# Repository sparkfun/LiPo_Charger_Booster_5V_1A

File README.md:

SparkFun LiPo Charger/Booster - 5V/1A
========================================

[*SparkFun LiPo Charger/Booster - 5V/1A (PRT-14411)*](https://www.sparkfun.com/products/14411)

The SparkFun 5V/1A LiPo Charger/Booster is a no-nonsense circuit for generating one amp from a Lithium Polymer battery at 5V.

Repository Contents
-------------------

* **/Documentation** - Data sheets, additional product information
* **/Hardware** - Eagle design files (.brd, .sch)
* **/Production** - Production panel files (.brd)

Documentation
--------------
* **[SparkFun Fritzing Part](https://github.com/sparkfun/Fritzing_Parts/blob/main/products/14411_sfe_LiPo_Charger_Booster-5V1A.fzpz)** - Fritzing diagrams for SparkFun products.
* **[Hookup Guide](https://learn.sparkfun.com/tutorials/sparkfun-5v1a-lipo-chargerbooster-hookup-guide)** - Basic hookup guide for the SparkFun LiPo Charger/Booster - 5V/1A.

Product Versions
----------------
* [PRT-14411](https://www.sparkfun.com/products/14411)- LiPo Charger/Booster 5V/1A

Version History
----------------
* [HW-V1.0](https://github.com/sparkfun/LiPo_Charger_Booster_5V_1A/releases/tag/HW-V1.0) 

License Information
-------------------

This product is _**open source**_! 

Please review the LICENSE.md file for license information. 

If you have any questions or concerns on licensing, please contact techsupport@sparkfun.com.

Distributed as-is; no warranty is given.

- Your friends at SparkFun.

_<COLLABORATION CREDIT>_

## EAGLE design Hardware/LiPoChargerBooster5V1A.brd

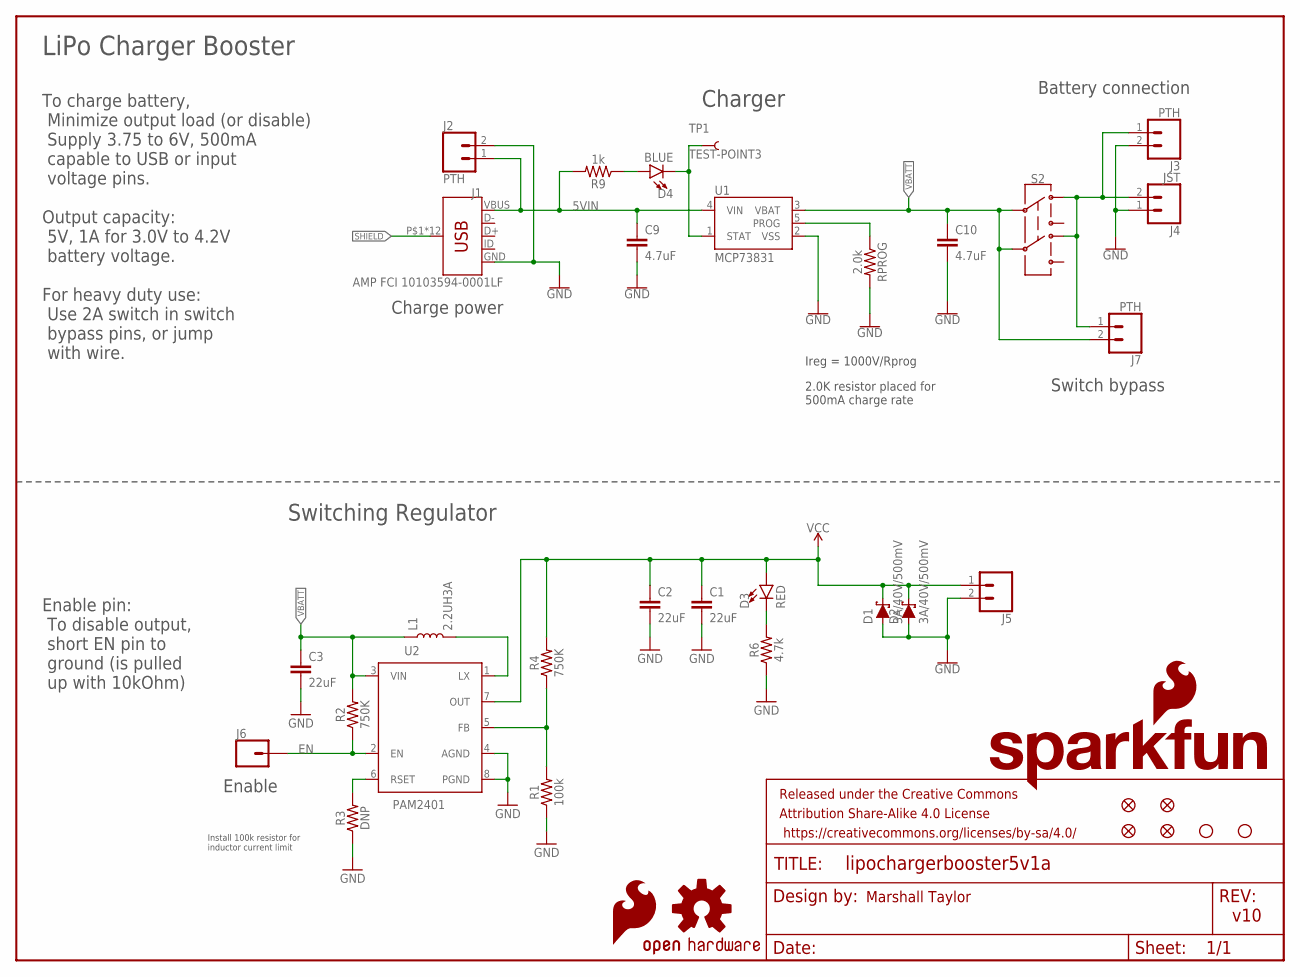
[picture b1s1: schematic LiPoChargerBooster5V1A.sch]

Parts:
C1, C2, C3: 22uF; 0805
C9, C10: 4.7uF; 0603
D1, D2: 3A/40V/500mV; SMA-DIODE
D3: RED; LED-0603
D4: BLUE; LED-0603
FRAME1: FRAME-LETTER; CREATIVE_COMMONS
J1: AMP FCI 10103594-0001LF; USB-MICROB-PTH
J2, J3, J7: PTH; 1X02
J4: JST; JST-2-SMD
J5: CONN_02; 1X02
J6: CONN_01; 1X01
JP1, JP2, JP4, JP16: FIDUCIAL1X2; FIDUCIAL-1X2
JP3: SFE_LOGO_NAME_FLAME.1_INCH; SFE_LOGO_NAME_FLAME_.1
JP6, JP7: STAND-OFF
L1: 2.2UH3A; INDUCTOR_4X4MM
LOGO1: SFE_LOGO_FLAME.1_INCH; SFE_LOGO_FLAME_.1
R1: 100k; 0603
R2, R4: 750K; 0603
R3: DNP; 0603
R6: 4.7k; 0603
R9: 1k; 0603
RPROG: 2.0k; 0603
S2: SWITCH-DPDT-SMD-AYZ0202; SWITCH_DPDT_SMD_AYZ0202
TP1: TEST-POINT3; PAD.03X.03
U1: MCP73831; SOT23-5
U2: PAM2401; MSOP8
U$1: OSHW-LOGOS; OSHW-LOGO-S

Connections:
5VIN: C9.1, J1.VBUS, J2.1, R9.2, U1.4 (VIN)
EN: J6.1, R2.1, U2.2 (EN)
GND: C1.2, C2.2, C3.2, C9.2, C10.2, D1.A, D2.A, J1.GND, J2.2, J3.2, J4.1 (2), J5.2, R1.1, R3.1, R6.1, RPROG.2, U1.2 (VSS), U2.4 (AGND), U2.8 (PGND)
unnamed: D3.C, R6.2
unnamed: D4.A, R9.1
unnamed: L1.P$2 (2), U2.1 (LX)
unnamed: R3.2, U2.6 (RSET)
unnamed: J3.1, J4.2 (1), J7.1, S2.1, S2.4
unnamed: RPROG.1, U1.5 (PROG)
unnamed: R1.2, R4.1, U2.5 (FB)
unnamed: D4.C, TP1.P$1, U1.1 (STAT)
SHIELD: J1.P$1 (SHIELD), J1.P$2 (SHIELD), J1.P$3 (SHIELD), J1.P$4 (SHIELD), J1.P$6 (SHIELD), J1.P$8 (SHIELD), J1.P$10 (SHIELD), J1.P$12 (SHIELD), J1.SHEILD2 (SHIELD), J1.SHIELD, J1.SHIELD3 (SHIELD), J1.SHIELD4 (SHIELD)
VBATT: C3.1, C10.1, J7.2, L1.P$1 (1), R2.2, S2.2, S2.5, U1.3 (VBAT), U2.3 (VIN)
VCC: C1.1, C2.1, D1.C, D2.C, D3.A, J5.1, R4.2, U2.7 (OUT)

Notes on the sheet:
Charger
Switching Regulator
Marshall Taylor
v10
2.0K resistor placed for 500mA charge rate
Ireg = 1000V/Rprog
To charge battery, Minimize output load (or disable) Supply 3.75 to 6V, 500mA capable to USB or input voltage pins.
Install 100k resistor for inductor current limit
LiPo Charger Booster
Output capacity: 5V, 1A for 3.0V to 4.2V battery voltage.
Enable pin: To disable output, short EN pin to ground (is pulled up with 10kOhm)
Enable
Charge power
Battery connection
Switch bypass
For heavy duty use: Use 2A switch in switch bypass pins, or jump with wire.

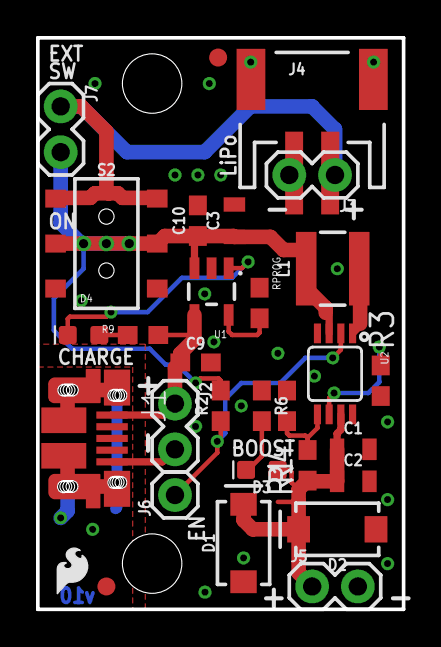
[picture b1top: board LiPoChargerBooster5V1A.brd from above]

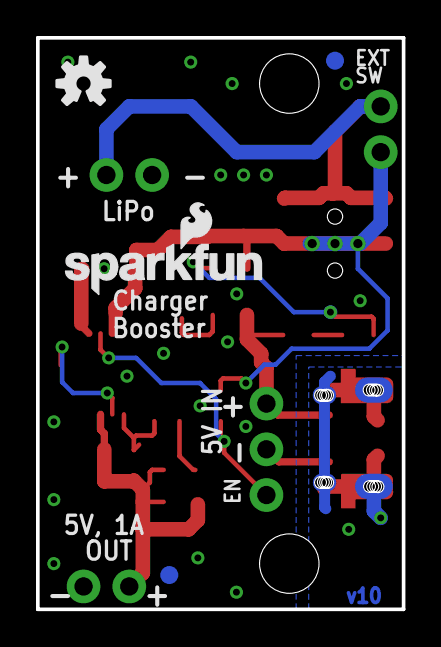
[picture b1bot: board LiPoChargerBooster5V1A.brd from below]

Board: 2 copper layers, 20.3 x 31.8 mm, 38 parts (5 on the bottom side), 14 nets.

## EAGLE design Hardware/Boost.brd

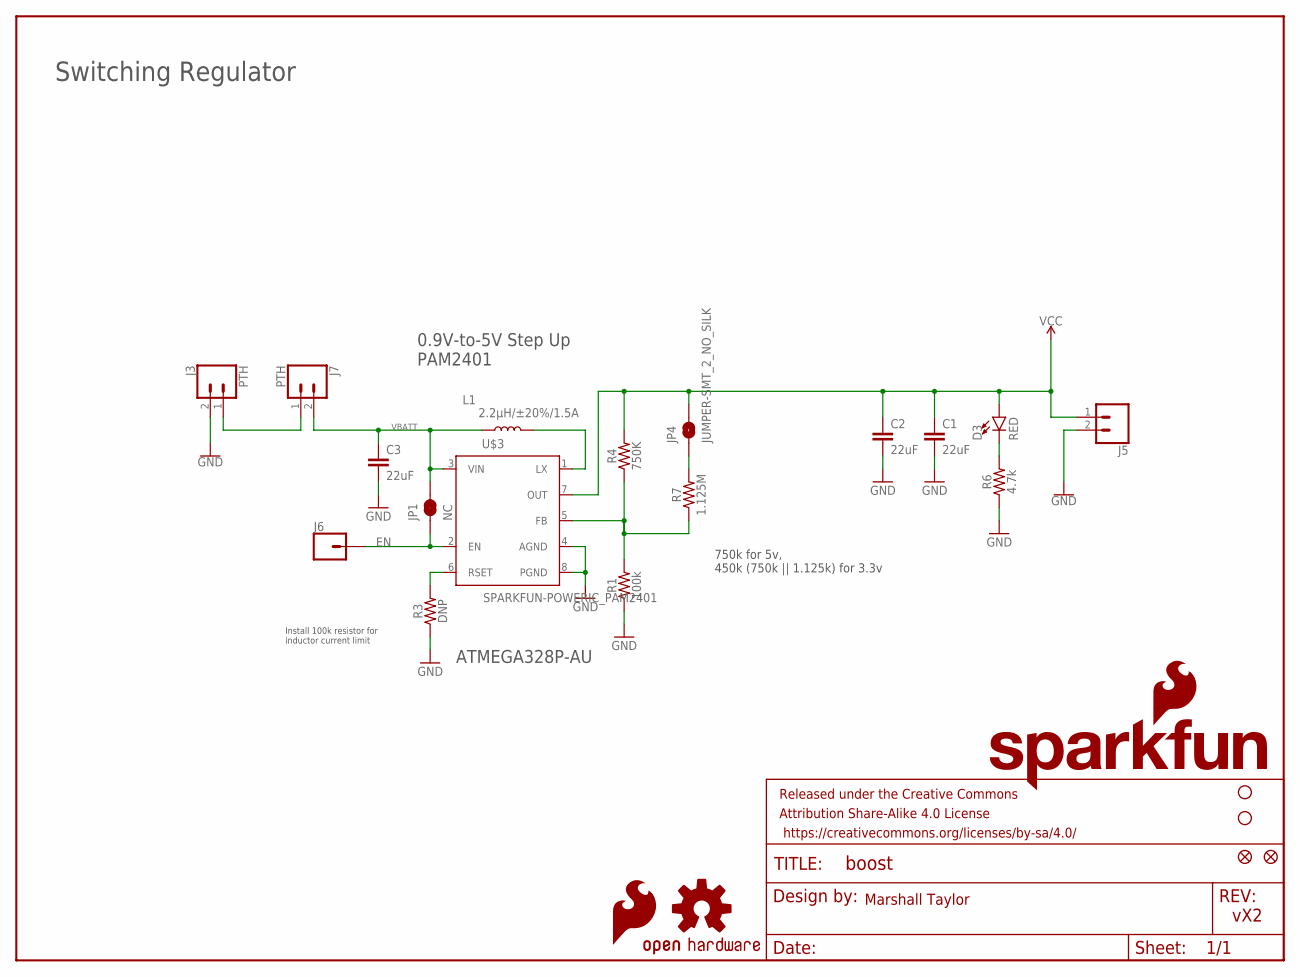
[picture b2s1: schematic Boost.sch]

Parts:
C1, C2, C3: 22uF; 0805
D3: RED; LED-0603
FRAME1: FRAME-LETTER; CREATIVE_COMMONS
J3, J7: PTH; 1X02_NO_SILK
J5: CONN_021X02_NO_SILK; 1X02_NO_SILK
J6: CONN_01; 1X01
JP1: NC; SMT-JUMPER_2_NC_TRACE_NO-SILK
JP2, JP16: FIDUCIAL1X2; FIDUCIAL-1X2
JP3: SFE_LOGO_NAME_FLAME.1_INCH; SFE_LOGO_NAME_FLAME_.1
JP4: JUMPER-SMT_2_NO_SILK; SMT-JUMPER_2_NO_SILK
JP6, JP7: STAND-OFF
L1: 2.2µH/±20%/1.5A; INDUCTOR_2.2UHCOPY
LOGO1: SFE_LOGO_FLAME.1_INCH; SFE_LOGO_FLAME_.1
R1: 100k; 0603
R3: DNP; 0603
R4: 750K; 0603
R6: 4.7k; 0603
R7: 1.125M; 0603
U$1: OSHW-LOGOS; OSHW-LOGO-S
U$3: SPARKFUN-POWERIC_PAM2401; SPARKFUN-POWERIC_MSOP8

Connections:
EN: J6.1, JP1.1, U$3.2 (EN)
GND: C1.2, C2.2, C3.2, J3.2, J5.2, R1.1, R3.1, R6.1, U$3.4 (AGND), U$3.8 (PGND)
unnamed: JP4.1, R7.2
unnamed: D3.C, R6.2
unnamed: L1.P$2 (2), U$3.1 (LX)
unnamed: R3.2, U$3.6 (RSET)
unnamed: J3.1, J7.1
unnamed: R1.2, R4.1, R7.1, U$3.5 (FB)
VBATT: C3.1, J7.2, JP1.2, L1.P$1 (1), U$3.3 (VIN)
VCC: C1.1, C2.1, D3.A, J5.1, JP4.2, R4.2, U$3.7 (OUT)

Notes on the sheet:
Switching Regulator
Marshall Taylor
vX2
0.9V-to-5V Step Up PAM2401
ATMEGA328P-AU
Install 100k resistor for inductor current limit
750k for 5v, 450k (750k || 1.125k) for 3.3v

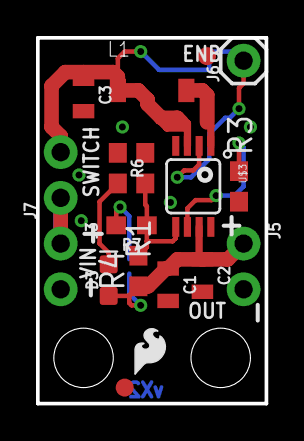
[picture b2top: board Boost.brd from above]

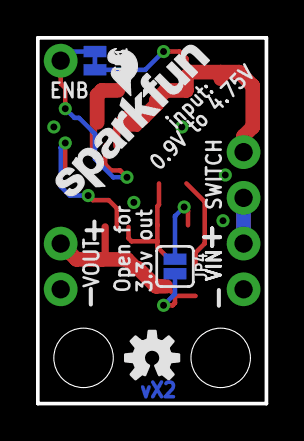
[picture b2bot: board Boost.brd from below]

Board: 2 copper layers, 12.7 x 20.3 mm, 25 parts (4 on the bottom side), 10 nets.

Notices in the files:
parts and their libraries:
SparkFun-Aesthetics: Licensing: CC v3.0 Share-Alike You are welcome to use this library for commercial purposes.
SparkFun-Aesthetics: Released under the Creative Commons Attribution Share-Alike 4.0 License
SparkFun-Aesthetics: https://creativecommons.org/licenses/by-sa/4.0
